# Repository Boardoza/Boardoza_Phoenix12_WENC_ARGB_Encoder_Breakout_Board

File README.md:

# Boardoza Phoenix12-WENC Breakout Board

The **Boardoza Phoenix-12WENC Breakout Board** is a compact and versatile lighting control board featuring **12 addressable ARGB LEDs** combined with an integrated **rotary encoder interface**. It is designed to provide interactive and dynamic lighting effects while maintaining high compatibility with a wide range of digital systems.

This board is especially suitable for projects that require **visual feedback and user interaction**, such as control panels, UI knobs, decorative lighting, and embedded interfaces. With support for both **CMOS and TTL logic levels** and flexible **THT and SMD connection options**, the Phoenix-12WENC can be easily integrated into prototypes as well as final products.

## [Click here to purchase!](https://www.ozdisan.com/ureticiler/boardoza)
| Front Side | Back Side |
|:---:|:---:|
|  |  |

---

## Key Features

- **12 Addressable ARGB LEDs:** Equipped with 12 individually controllable ARGB LEDs (T3A33BRG-H9C0002X1U1930) for smooth and vibrant lighting effects.
- **Rotary Encoder Support:** Enables intuitive and real-time control of lighting modes, brightness, and effects through user interaction.
- **Flexible Signal Routing:** Provides DIN, CIN, DOUT, and COUT connections for easy daisy-chaining and signal continuity.
- **Dual Logic Compatibility:** Supports both CMOS and TTL logic levels, ensuring compatibility with a wide range of controllers and systems.
- **Multiple Connection Options:** Features both THT (Through-Hole) and SMD (Surface-Mount) pads for flexible assembly and design integration.
- **Designed for Interactive Applications:** Ideal for user interfaces, control panels, decorative lighting, and visual feedback systems.

---

## Technical Specifications

**Model:** Phoenix-12WENC    
**Manufacturer:** Boardoza  
**Functions:** Addressable RGB LED control with rotary encoder input  
**Input Voltage:** 3.3 V / 5 V  
**LED Model:** T3A33BRG-H9C0002X1U1930  
**Number of LEDs:** 12  
**LED Type:** Individually addressable RGB LEDs  
**Logic Compatibility:** TTL & CMOS  
**Data Interface:** Serial Data & Clock (DIN / CIN / DOUT / COUT)   
**Encoder Outputs:** Terminal A, Terminal B, Switch (Active Low)  
**Daisy-Chain Support:** Yes  
**Operating Temperature:** -40 °C to +85 °C  
**Board Dimensions:** 44.58 mm × 44.56 mm  

---

## Board Pinout

### ( J1 ) Data Output

| Pin Number | Pin Name | Description |
|:---:|:---:|---|
| 1 | DOUT | Series data output |

### ( J2 ) Clock Output

| Pin Number | Pin Name | Description |
|:---:|:---:|---|
| 1 | COUT | Clock output |

### ( J3 ) Data Input

| Pin Number | Pin Name | Description |
|:---:|:---:|---|
| 1 | DIN | Series data input |

### ( J4 ) Clock Input

| Pin Number | Pin Name | Description |
|:---:|:---:|---|
| 1 | CIN | Clock input |

### ( J5 ) Ground

| Pin Number | Pin Name | Description |
|:---:|:---:|---|
| 1 | GND | Ground |

### ( J6 ) Ground

| Pin Number | Pin Name | Description |
|:---:|:---:|---|
| 1 | GND | Ground |

### ( J7 ) Power

| Pin Number | Pin Name | Description |
|:---:|:---:|---|
| 1 | VCC | Power supply (3.3V / 5V) |

### ( J8 ) Power

| Pin Number | Pin Name | Description |
|:---:|:---:|---|
| 1 | VCC | Power supply (3.3V / 5V) |

### ( J9 ) Encoder Output B

| Pin Number | Pin Name | Description |
|:---:|:---:|---|
| 1 | Terminal_B | Encoder Channel B Output |

### ( J10 ) Encoder Output A

| Pin Number | Pin Name | Description |
|:---:|:---:|---|
| 1 | Terminal_A | Encoder Channel A Output |

### ( J11 ) Encoder Switch

| Pin Number | Pin Name | Description |
|:---:|:---:|---|
| 1 | SW | Push Button Output (Active Low) |  

---

## Board Dimensions

---

## Step Files

[Boardoza Phoenix-12WENC.step](./assets/Phoenix-12WENC%20Step.step)

---

## Datasheets

[T3A33BRG ARGB LED Datasheet](./assets/Phoenix-12WENC%20Datasheet.pdf)  
[Rotary Encoder Datasheet](./assets/Rotary%20Encoder%20Datasheet.pdf)

---

## Version History

- **V1.0.0** – Initial Release

---

## Support

- For questions or technical support, please contact **support@boardoza.com**

---

## **License**

This repository contains both hardware and software components:

### **Hardware Design**

[![CC BY-SA 4.0][cc-by-sa-shield]][cc-by-sa]

All hardware design files are licensed under [Creative Commons Attribution-ShareAlike 4.0 International License][cc-by-sa].

[cc-by-sa]: http://creativecommons.org/licenses/by-sa/4.0/
[cc-by-sa-shield]: https://img.shields.io/badge/License-CC%20BY--SA%204.0-lightgrey.svg

### **Software/Firmware**

[![BSD-3-Clause][bsd-shield]][bsd]

All software and firmware are licensed under [BSD 3-Clause License][bsd].

[bsd]: https://opensource.org/licenses/BSD-3-Clause
[bsd-shield]: https://img.shields.io/badge/License-BSD%203--Clause-blue.svg

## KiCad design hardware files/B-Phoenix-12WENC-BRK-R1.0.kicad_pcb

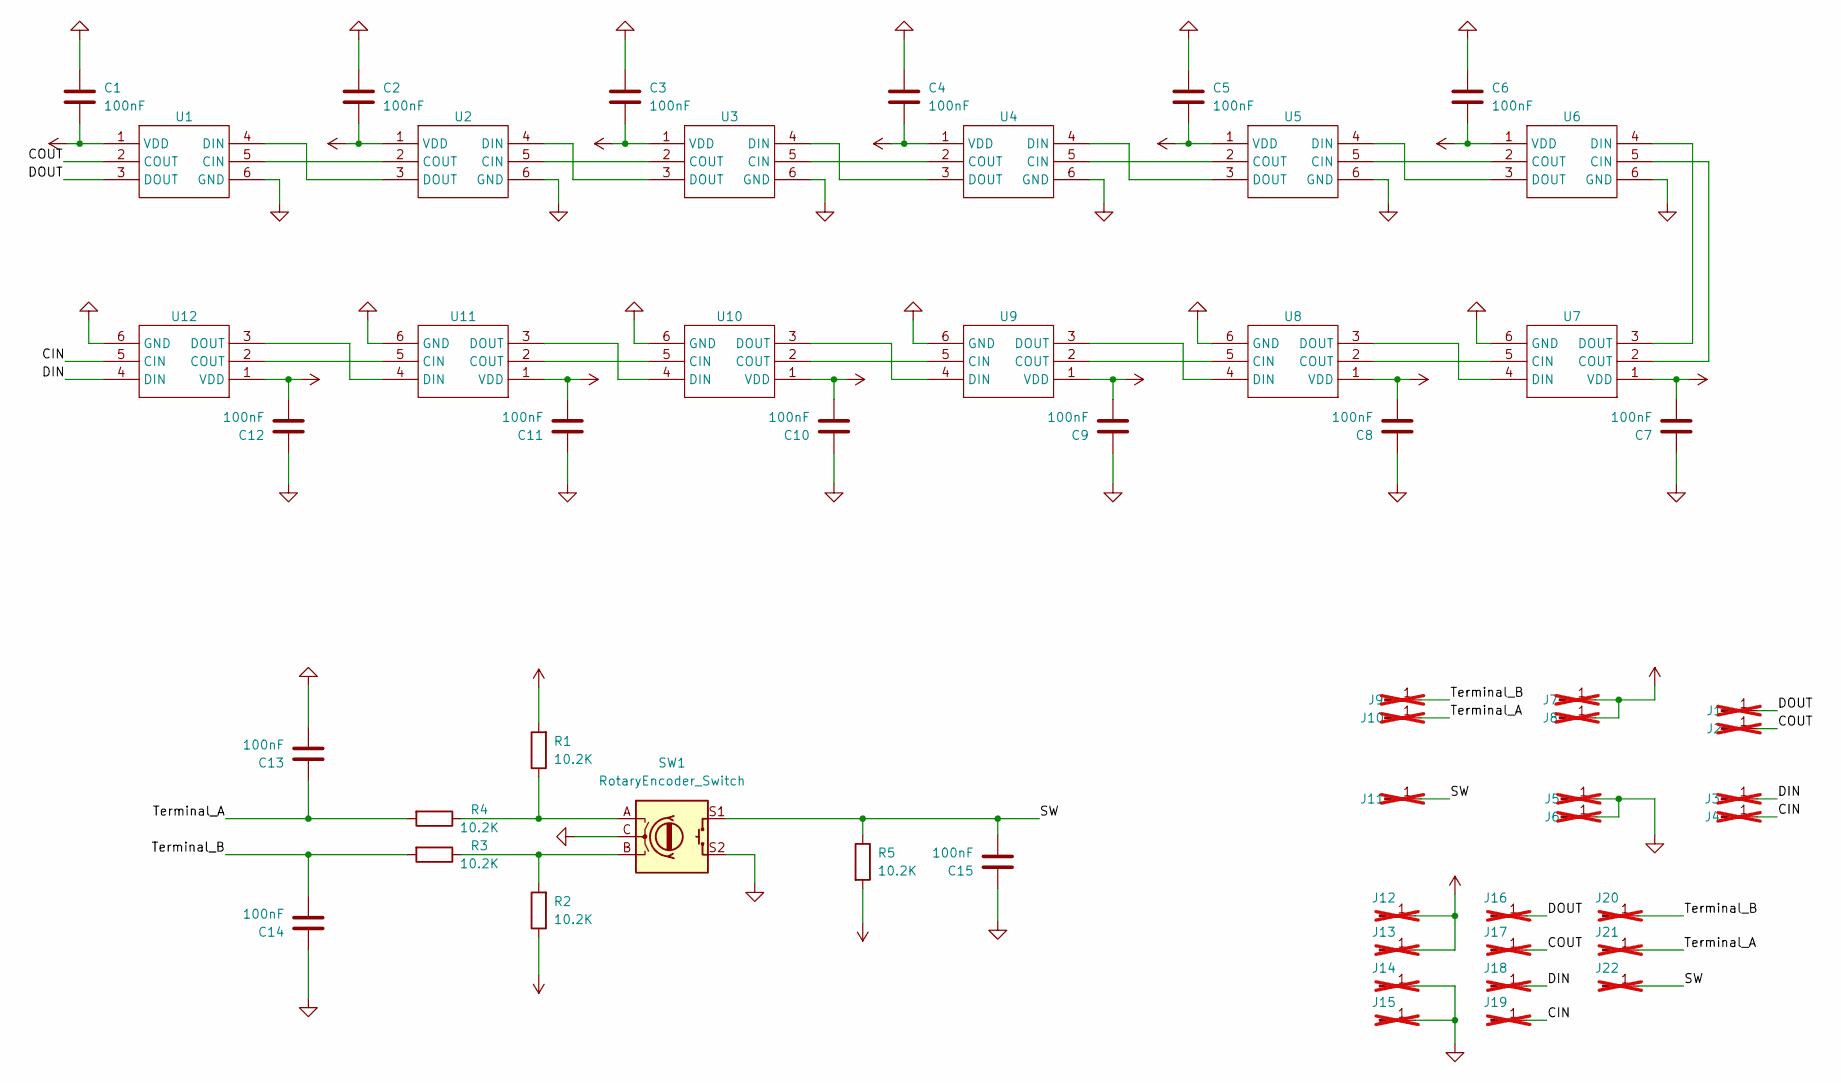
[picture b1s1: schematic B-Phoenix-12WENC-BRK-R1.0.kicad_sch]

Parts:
C1, C2, C3, C4, C5, C6, C7, C8, C9, C10, C11, C12, C13, C14, C15: 100nF; C_0603_1608Metric; MPN MCF03KTB500104
J1, J2, J3, J4, J5, J6, J7, J8, J9, J10, J11: Conn_01x01_Pin; PinHeader_1x01_P2.54mm_Vertical; not fitted
J12, J13, J14, J15, J16, J17, J18, J19, J20, J21, J22: Conn_01x01_Pin; SolderWirePad_1x01_SMD_1x2mm; not fitted
R1, R2, R3, R4, R5: 10.2K; R_0603_1608Metric; MPN 0603SAF1022T5E
SW1: RotaryEncoder_Switch; L-KLS4-EC1123S-E-5A-F20; MPN L-KLS4-EC1123S-E-5A-F20
U1, U2, U3, U4, U5, U6, U7, U8, U9, U10, U11, U12: T3A33BRG-H9C0002X1U1930_HVK; MPN T3A33BRG-H9C0002X1U1930

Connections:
/CIN: J4.1, J19.1, U12.5 (CIN)
/COUT: J2.1, J17.1, U1.2 (COUT)
/DIN: J3.1, J18.1, U12.4 (DIN)
/DOUT: J1.1, J16.1, U1.3 (DOUT)
/SW: C15.2, J11.1, J22.1, R5.1, SW1.S1
/Terminal_A: C13.1, J10.1, J21.1, R4.2
/Terminal_B: C14.2, J9.1, J20.1, R3.2
GND: C1.1, C2.1, C3.1, C4.1, C5.1, C6.1, C7.1, C8.1, C9.1, C10.1, C11.1, C12.1, C13.2, C14.1, C15.1, J5.1, J6.1, J14.1, J15.1, SW1.C, SW1.MP, SW1.S2, U1.6 (GND), U2.6 (GND), U3.6 (GND), U4.6 (GND), U5.6 (GND), U6.6 (GND), U7.6 (GND), U8.6 (GND), U9.6 (GND), U10.6 (GND), U11.6 (GND), U12.6 (GND)
unnamed: R1.1, R4.1, SW1.A
unnamed: R2.2, R3.1, SW1.B
unnamed: U1.5 (CIN), U2.2 (COUT)
unnamed: U1.4 (DIN), U2.3 (DOUT)
unnamed: U2.5 (CIN), U3.2 (COUT)
unnamed: U2.4 (DIN), U3.3 (DOUT)
unnamed: U3.5 (CIN), U4.2 (COUT)
unnamed: U3.4 (DIN), U4.3 (DOUT)
unnamed: U4.5 (CIN), U5.2 (COUT)
unnamed: U4.4 (DIN), U5.3 (DOUT)
unnamed: U5.5 (CIN), U6.2 (COUT)
unnamed: U5.4 (DIN), U6.3 (DOUT)
unnamed: U6.5 (CIN), U7.2 (COUT)
unnamed: U6.4 (DIN), U7.3 (DOUT)
unnamed: U7.5 (CIN), U8.2 (COUT)
unnamed: U7.4 (DIN), U8.3 (DOUT)
unnamed: U8.5 (CIN), U9.2 (COUT)
unnamed: U8.4 (DIN), U9.3 (DOUT)
unnamed: U10.5 (CIN), U11.2 (COUT)
unnamed: U9.5 (CIN), U10.2 (COUT)
unnamed: U10.4 (DIN), U11.3 (DOUT)
unnamed: U9.4 (DIN), U10.3 (DOUT)
unnamed: U11.5 (CIN), U12.2 (COUT)
unnamed: U11.4 (DIN), U12.3 (DOUT)
VCC: C1.2, C2.2, C3.2, C4.2, C5.2, C6.2, C7.2, C8.2, C9.2, C10.2, C11.2, C12.2, J7.1, J8.1, J12.1, J13.1, R1.2, R2.1, R5.2, U1.1 (VDD), U2.1 (VDD), U3.1 (VDD), U4.1 (VDD), U5.1 (VDD), U6.1 (VDD), U7.1 (VDD), U8.1 (VDD), U9.1 (VDD), U10.1 (VDD), U11.1 (VDD), U12.1 (VDD)

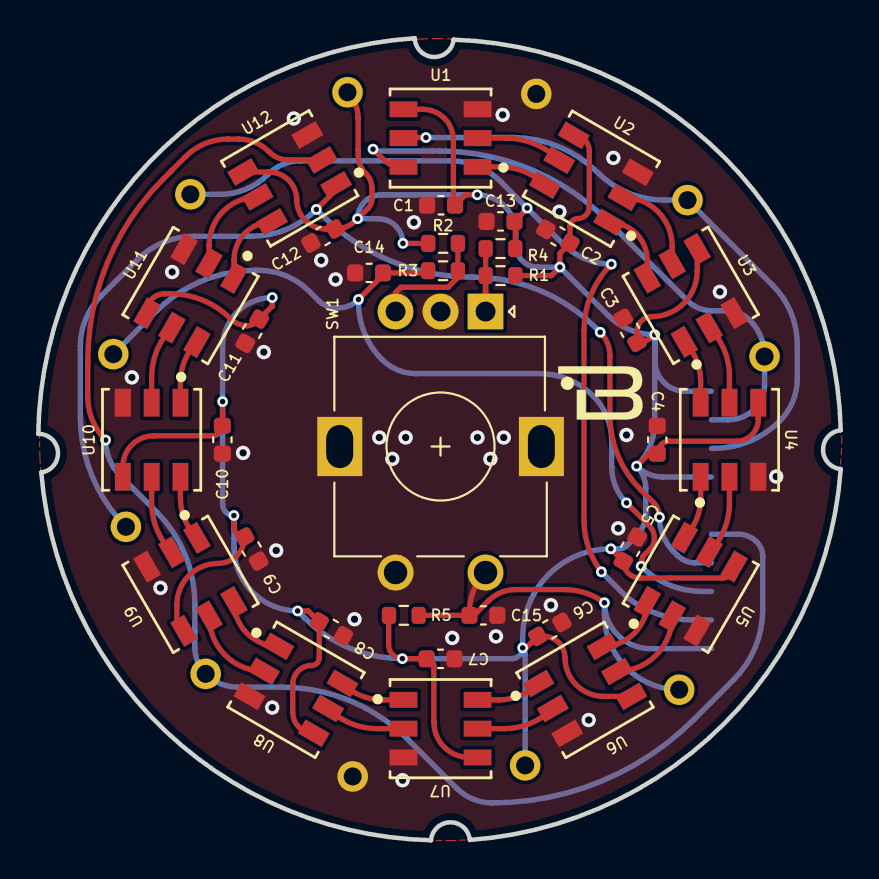
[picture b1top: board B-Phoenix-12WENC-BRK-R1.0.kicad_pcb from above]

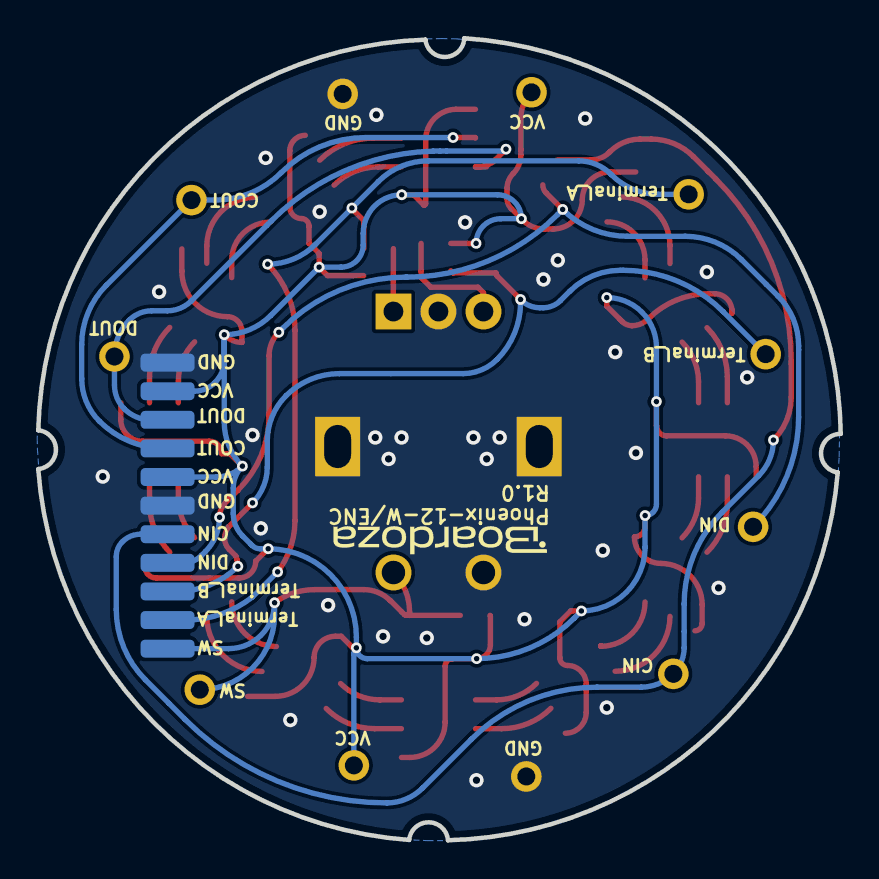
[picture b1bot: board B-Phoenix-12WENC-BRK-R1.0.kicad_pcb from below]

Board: 2 copper layers, 44.6 x 44.6 mm, 53 parts (11 on the bottom side), 33 nets.

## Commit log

2026-04-28 Fix hueOffset declaration formatting
2026-04-28 Fixed comment lines
2026-04-28 Refactor comments in EC1101S.cpp
    Updated comments for clarity and consistency in English.
